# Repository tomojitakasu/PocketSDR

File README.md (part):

# **Pocket SDR - An Open-Source GNSS SDR,<br> ver. 0.22**

<div style="text-align: right;">
<strong>2026-11-03</strong>
</div>

---

## **Overview**

**Pocket SDR** is an open-source Global Navigation Satellite System (GNSS) receiver based
on software-defined radio (SDR) technology. It consists of RF frontend devices named
**Pocket SDR FE**, utilities for these devices, and GNSS SDR applications (APs) written
in Python, C, and C++. It supports almost all signals for **GPS**, **GLONASS**, **Galileo**,
**QZSS**, **BeiDou**, **NavIC**, and **SBAS**.

The Pocket SDR FE device includes 2, 4, or 8 RF frontend channels, supporting the
GNSS L1 band (1525 - 1610 MHz) or L2/L5/L6 bands (1160 - 1290 MHz). For these signal bands, refer to [**GNSS Signal Bands**](https://github.com/tomojitakasu/PocketSDR/blob/master/doc/signal_bands.pdf). Each RF channel
of the Pocket SDR FE device provides IF (intermediate-frequency) bandwidth of up to 36 MHz. The ADC sampling rate can be configured up to 32 Msps (FE 2CH) or 48 Msps (FE 4CH and FE 8CH).

Pocket SDR also includes utility programs to configure the Pocket SDR FE devices,
capture, and dump digitized IF data.
Additionally, Pocket SDR provides GNSS SDR APs to display the PSD (power spectrum density) of captured IF data, search for GNSS signals, track these signals, decode navigation data, and generate PVT (position, velocity, and time) solutions.
These utilities and APs are compatible with **Windows**, **Linux**, **Raspberry Pi OS**, **macOS**, and other environments.

The supported GNSS signals by Pocket SDR are as follows. For details on these signals and Pocket SDR signal IDs, refer to
[**GNSS Signals**](https://github.com/tomojitakasu/PocketSDR/blob/master/doc/signal_IDs.pdf).

* **GPS**: L1C/A, L1C-D, L1C-P, L2C-M, L5-I, L5-Q
* **GLONASS**: L1C/A (L1OF), L2C/A (L2OF), L1OCd, L1OCp, L2OCp, L3OCd, L3OCp
* **Galileo**: E1-B, E1-C, E5a-I, E5a-Q, E5b-I, E5b-Q, E5AltBOC (E5abQ), E6-B, E6-C
* **QZSS**: L1C/A, L1C/B, L1C-D, L1C-P, L1S, L2C-M, L5-I, L5-Q, L5S-I, L5S-Q, L6D, L6E
* **BeiDou**: B1I, B1C-D, B1C-P, B2a-D, B2a-P, B2I, B2b-I, B3I
* **NavIC**: L1-SPS-D, L1-SPS-P, L5-SPS
* **SBAS**: L1C/A, L5-I, L5-Q

These utilities and APs are written in Python, C, and C++ in a compact and modular way,
making them easy to modify for adding custom algorithms.

In addition to the Pocket SDR FE devices, Pocket SDR supports third-party
SDR hardware (**USRP**, **LimeSDR**, **bladRF**, **PlutoSDR**, **RTL-SDR**, and so on) via 
[**SoapySDR**](https://github.com/pothosware/SoapySDR/wiki).
See [**SoapySDR Device Notes**](https://github.com/tomojitakasu/PocketSDR/blob/master/doc/notes_soapy_dev.md) for verified devices,
installation notes, and device-specific caveats.

<p align="center">
  
  <b>Pocket SDR FE 2CH (v.2.0 and v.2.3), FE 4CH</b>
</p>

<p align="center">
  
  <b>Pocket SDR FE 8CH (2-RF-inputs and 8-RF-inputs)</b>
</p>

<p align="center">
  
  <b>GUI-based Real-Time GNSS SDR Receiver AP</b>
</p>

--------------------------------------------------------------------------------
<div class="pagebreak"></div>

## **Documents**

- Pocket SDR C Library API Reference
(https://github.com/tomojitakasu/PocketSDR/tree/master/doc/api_ref.pdf)

- Pocket SDR Command Reference
(https://github.com/tomojitakasu/PocketSDR/tree/master/doc/command_ref.pdf)

- Pocket SDR GNSS SDR Algorithm Description
(https://github.com/tomojitakasu/PocketSDR/tree/master/doc/algo_desc.pdf)

- Pocket SDR GNSS SDR アルゴリズム解説
(https://github.com/tomojitakasu/PocketSDR/tree/master/doc/algo_desc_jp.pdf)

- T.Takasu, An Open Source GNSS SDR: Development and Application, IPNTJ Next GNSS
Technology WG, February 21, 2022
(https://gpspp.sakura.ne.jp/paper2005/IPNTJ_NEXTWG_202202.pdf)

- T.Takasu, Development of QZSS L6 Receiver without Pilot Signal by using SDR,
IPNTJ Annual Conference, June 10, 2022
(https://gpspp.sakura.ne.jp/paper2005/IPNTJ_20220610.pdf)

- T.Takasu, Pocket SDR: Design, Implementation and Applications, A seminar for
GNSS Software Defined Receivers, Nov 19, 2024
(https://gpspp.sakura.ne.jp/paper2005/pocketsdr_seminar_202411_revA.pdf)

--------------------------------------------------------------------------------
<div class="pagebreak"></div>

## **Directory Structure and Contents**
```
PocketSDR
├── bin         # Pocket SDR APs binary programs
├── app         # Pocket SDR APs source programs
│   ├── pocket_conf  # Pocket SDR FE device configurator
│   ├── pocket_dump  # Dump digital IF data of Pocket SDR FE device
│   ├── pocket_scan  # Scan and list USB devices
│   ├── pocket_acq   # GNSS signal acquisition
│   ├── pocket_trk   # GNSS signal tracking and PVT generation
│   ├── pocket_web   # GNSS receiver server with Web UI
│   ├── pocket_snap  # Snapshot Positioning
│   ├── pocket_calib # Antenna array attitude / per-CH bias calibration
│   ├── convbin      # RINEX converter supporting Pocket SDR
│   └── str2str      # Stream converter (RTKLIB-derived)
├── src         # Pocket SDR library source programs
├── html        # Web UI files served by pocket_web (JS + CSS, no build step)
├── python      # Pocket SDR Python scripts (incl. pocket_sdr.py GUI)
├── lib         # Libraries for APs and Python scripts
│   ├── win32        # Built libraries for Windows (UCRT64)
│   ├── macos        # Built libraries for macOS
│   ├── linux        # Built libraries for Linux or Raspberry Pi OS
│   ├── build        # Makefiles to build libraries (UCRT64 / Linux / macOS)
│   ├── cyusb        # Cypress EZ-USB API (CyAPI.a) and includes
│   ├── RTKLIB       # RTKLIB source programs based on 2.4.3 b34
│   ├── pocketfft    # PocketFFT (header-only FFT, used internally)
│   └── SoapySDR     # SoapySDR headers + import lib for SDR device support
├── conf        # Configuration files for Pocket SDR FE
├── FE_2CH      # Pocket SDR FE 2CH H/W and F/W
├── FE_4CH      # Pocket SDR FE 4CH H/W and F/W
├── FE_8CH      # Pocket SDR FE 8CH H/W and F/W (3-bit RF samples)
├── driver      # Driver installation instruction for Pocket SDR FE
├── doc         # Documents (incl. api_ref.md, command_ref.md)
├── image       # Image files for documents
├── sample      # Sample digital IF data captured by Pocket SDR FE
└── test        # Test codes, scripts and data
    ├── python       # Python scripts for tests
    ├── script       # Shell scripts for tests
    ├── src          # source programs for tests
    └── utest        # makefile for unit tests

```
--------------------------------------------------------------------------------
<div class="pagebreak"></div>

## **Installation for Windows**

* Download and extract PocketSDR.zip or clone the git repository [**here**](https://github.com/tomojitakasu/PocketSDR) to an appropriate directory <install_dir>.
to an appropriate directory <install_dir>.
```
> unzip PocketSDR.zip
or
> git clone https://github.com/tomojitakasu/PocketSDR
```
* Install USB device driver for Pocket SDR FE according to [**driver/readme.txt**](https://github.com/tomojitakasu/PocketSDR/blob/master/driver/readme.txt)
.
* Install [**Python**](https://www.python.org/) with checking "Add python.exe to PATH".
* Install additional python packages as follows.
```
> pip install numpy scipy matplotlib
```
* (Optional) To use SoapySDR-supported devices (LimeSDR, HackRF, RTL-SDR,
  bladeRF, etc.), install [**radioconda**](https://github.com/ryanvolz/radioconda)
  and add `<radioconda_install_dir>\Library\bin` to PATH. See
  [SoapySDR Device Notes](https://github.com/tomojitakasu/PocketSDR/blob/master/doc/notes_soapy_dev.md#windows) for per-device
  packages, Zadig driver setup, and bladeRF version caveats.
* Add the Pocket SDR binary programs path (<install_dir>\PocketSDR\bin) to 
  the command search path (Path) of Windows environment variables.
* Add the Pocket SDR Python scripts path (<install_dir>\PocketSDR\python) to 
  the command search path (Path) of Windows environment variables.

--------------------------------------------------------------------------------

## **To rebuild binary programs for Windows**
* If you want to rebuild the binary utilities, APs, or shared libraries for the python APs
for Windows, you need [**MSYS2**](https://www.msys2.org/) with the **UCRT64** environment.
The UCRT64 toolchain links against the same C runtime (`ucrtbase.dll`) as
[**radioconda**](https://github.com/ryanvolz/radioconda)'s SoapySDR DLLs, which
gives stable high-rate streaming with SDR hardware (e.g., LimeSDR at 64 Msps).
The legacy **MINGW64** environment also builds, but suffers significant
performance loss with SoapySDR devices due to msvcrt/UCRT mixing.

* Open the **MSYS2 UCRT64** shell and install the development tools and the
  Python stack used by the python APs:
```
$ pacman -Syy
$ pacman -S git make
$ pacman -S mingw-w64-ucrt-x86_64-gcc
$ pacman -S mingw-w64-ucrt-x86_64-binutils
$ pacman -S mingw-w64-ucrt-x86_64-python
$ pacman -S mingw-w64-ucrt-x86_64-python-numpy
$ pacman -S mingw-w64-ucrt-x86_64-python-scipy
$ pacman -S mingw-w64-ucrt-x86_64-python-matplotlib
```
* If you intend to use SoapySDR-supported devices, install radioconda first.
  The default radioconda location used by the Makefiles is
  `/c/Users/<user>/radioconda/Library`. If installed elsewhere, override
  with `SOAPY_ROOT` on the make command line. See
  [SoapySDR Device Notes](https://github.com/tomojitakasu/PocketSDR/blob/master/doc/notes_soapy_dev.md#windows-build-notes)
  for details.

* If SoapySDR device support is not required, build `libsdr`, `pocket_trk`,
  and `pocket_dump` with `USE_SOAPY=0`. Pocket SDR FE USB devices and
  IF-file based processing still work; only SoapySDR device input is
  disabled. If you are rebuilding an existing tree, run `make clean` first.
```
$ cd <install_dir>/lib/build
$ make clean && make USE_SOAPY=0 && make install
$ cd <install_dir>/app/pocket_trk
$ make clean && make USE_SOAPY=0 && make install
$ cd <install_dir>/app/pocket_dump
$ make clean && make USE_SOAPY=0 && make install
```

* Move to the library build directory and build libraries.
```
$ cd <install_dir>/lib/build
$ make
$ make install
```
  The default radioconda location is `/c/Users/<user>/radioconda/Library`. If
  installed elsewhere, override on the command line:
```
$ make SOAPY_ROOT=/c/path/to/radioconda/Library
```

* Move to the application program directory and build utilities and APs.
```
$ cd <install_dir>/app
$ make
$ make install
```

* To run unit tests for the libraries:
```
$ cd <install_dir>/test/utest
$ make
$ make test
==> test_sdr_array.exe
test_sdr_array_new_free_api ... OK
test_sdr_array_ant_pos_api ... OK
t...
test_sdr_usb_req_control ... OK
```

--------------------------------------------------------------------------------
<div class="pagebreak"></div>

## **Installation for Linux or Raspberry Pi OS**

> **Note**: Pocket SDR has been verified on Ubuntu / Debian-based Linux
> distributions and on **Raspberry Pi OS (Bookworm) on Raspberry Pi 5**
> (aarch64). The Pi 5 has been confirmed to handle Pocket SDR FE and the
> apt-installed SoapySDR devices for typical L1 / L2 single-channel use;
> see the **Notes for Raspberry Pi 5** subsection below for hardware
> caveats (USB power, USB 3.0 routing, CPU limits).

* You need fundamental development packages and some libraries. Confirm the following
packages installed: git, gcc, g++, make, libusb-1.0-0-dev, libfftw3-dev, python3, python3-numpy,
python3-scipy, python3-matplotlib, python3-tk
* (Optional) To use SoapySDR-supported devices (LimeSDR, HackRF, RTL-SDR,
  SDRPlay, bladeRF, etc.), install SoapySDR and the per-device modules:
```
$ sudo apt install libsoapysdr-dev soapysdr-tools soapysdr-module-all
```
  See [SoapySDR Device Notes](https://github.com/tomojitakasu/PocketSDR/blob/master/doc/notes_soapy_dev.md#linux--raspberry-pi-os)
  for per-device package names, udev access, UHD image installation, and
  the Ubuntu 24.04 bladeRF module update workaround.

* Download and extract PocketSDR.zip or clone the git repository to an appropriate directory <install_dir>.
```
$ unzip PocketSDR.zip
or
$ git clone https://github.com/tomojitakasu/PocketSDR
```
* Move to the library build directory and build libraries.
```
$ cd <install_dir>/lib/build
$ make
$ make install
```
* Move to the application program directory and build utilities and APs.
```
$ cd <install_dir>/app
$ make
$ make install
```
* Add the Pocket SDR binary programs path (<install_dir>/PocketSDR/bin) to the command search path.

* (Recommended) Install the udev rule so the Pocket SDR FE device is
  accessible to a normal user account (no `sudo` required). The repository
  ships a ready-to-use rule at [`driver/99-pocket-sdr.rules`](https://github.com/tomojitakasu/PocketSDR/blob/master/driver/99-pocket-sdr.rules) that grants the
  `plugdev` group read/write access to Pocket SDR FE 2CH (Cypress
  EZ-USB FX2LP, VID `04B4` / PID `1004`) and FE 4CH / 8CH (Cypress
  EZ-USB FX3, VID `04B4` / PID `00F1`):
```
$ sudo cp <install_dir>/driver/99-pocket-sdr.rules /etc/udev/rules.d/
$ sudo udevadm control --reload-rules && sudo udevadm trigger
$ sudo usermod -aG plugdev $USER     # add yourself to plugdev
```
  Log out and back in (or reboot) so the new group membership takes effect,
  then unplug and re-plug the device. After that, `pocket_scan`,
  `pocket_conf`, `pocket_dump`, `pocket_trk`, and `pocket_sdr.py` all run
  without `sudo`.

  Verify the rule is in effect:
```
$ lsusb -d 04b4:                         # confirm the device is enumerated
$ ls -l /dev/bus/usb/<bus>/<dev>          # group should be "plugdev", mode 0660
$ pocket_scan                             # should list the device
```
  If your distribution uses a different group than `plugdev` (e.g.
  `dialout` on some systems, or systemd-logind's `uaccess` is sufficient
  on its own), adjust `GROUP=` in the rule file or rely on the
  `TAG+="uaccess"` line which grants access to the currently logged-in
  seat user on systemd-based systems.

* If you skip the udev rule, you must run the Pocket SDR utilities under
  `sudo` to access the USB device:
```
$ sudo pocket_conf ../conf/pocket_L1L6_12MHz.conf
$ sudo pocket_dump -t 10 ch1.bin ch2.bin
$ sudo pocket_sdr.py
```

### **Notes for Raspberry Pi 5**

Raspberry Pi 5 (Cortex-A76 4-core @ 2.4 GHz, aarch64) runs the same
build path as desktop Linux above. The Makefiles auto-detect aarch64
and enable NEON SIMD optimizations (`-DNEON`). A few Pi-specific
constraints to be aware of:

* **USB power budget**: Pi 5 advertises 5V / 5A on the official PSU but
  the USB ports share a ~1.6 A budget. USRP B210 (~2 A peak), Pocket
  SDR FE 8CH, and BladeRF 2.0 typically need either a USB Y-cable
  (separate +5V feed) or a **self-powered (externally-fed) USB hub**.
  Symptoms of insufficient power are intermittent USB resets, FPGA
  bitstream upload failures (USRP), and dropped samples.

* **USB 3.0 routing**: Pi 5 has 2× USB 3.0 + 2× USB 2.0 ports. Always
  connect high-rate SDRs (LimeSDR, USRP B210, Pocket SDR FE 8CH) to a
  USB 3.0 port. Verify enumeration speed with:
```
$ lsusb -t
```
  The relevant device should show `5000M` (USB 3.0) ? `480M` means the
  device fell back to USB 2.0, which is bandwidth-limited and will drop
  samples at high rates.

* **CPU / sample rate limits**: Pi 5 holds up well thanks to NEON SIMD
  acceleration. Measured load (`pocket_trk` realtime, single-band L1
  tracking, all-in-view PRNs):

  | Device | Sample rate × tracked channels | CPU load (of 400% = 4 cores) |
  |---|---|---|
  | LimeSDR USB | 32 Msps × 7 ch | ~280% |
  | USRP B210 | 32 Msps × 8 ch | ~290% |
  | PlutoSDR | 6 Msps × 10 ch | ~121% |
  | RTL-SDR | 2.4 Msps × 16 ch | ~102% |

  32 Msps with many tracked channels is workable but leaves limited
  headroom for additional bands or PVT processing. **8 Msps** is a
  comfortable sweet spot for general L1 use on Pi 5. Heavier configs
  (LimeSDR 60 Msps × 2-band, Pocket SDR FE 8CH × multi-band) will
  saturate the Pi 5 CPU and are intended for desktop use.

* **PocketFFT vs FFTW3**: PocketFFT (default) works on aarch64 with
  NEON. If FFT becomes a bottleneck for your workload, FFTW3 is
  marginally faster on large transforms ? install with
  `sudo apt install libfftw3-dev` and switch the build per the
  [Using FFTW3 instead of PocketFFT](#using-fftw3-instead-of-pocketfft-optional)
  section below.

* **Storage**: For long IF data captures (`pocket_dump -t <long>`,
  `pocket_trk -raw`), use a USB 3.0 SSD or NVMe HAT. The microSD card
  on stock Pi 5 cannot sustain >50 MB/s writes for extended periods
  and will drop samples.

--------------------------------------------------------------------------------
<div class="pagebreak"></div>

## **Installation for macOS**

> **Note**: Verified on Apple Silicon (arm64). Pocket SDR FE 2/4/8CH (USB)
> has been confirmed working. For SoapySDR devices on macOS, see
> [SoapySDR Device Notes](https://github.com/tomojitakasu/PocketSDR/blob/master/doc/notes_soapy_dev.md#macos).

* You need [**Homebrew**](https://brew.sh) as a base package manager. Install
  Homebrew by following the instructions on its site, then install
  development tools:
```
$ brew install libusb fftw
```

* (Optional) Install [**radioconda**](https://github.com/ryanvolz/radioconda)
  to use SoapySDR devices and a self-contained Python environment:
```
$ curl -L -O https://github.com/ryanvolz/radioconda/releases/latest/download/Radioconda-MacOSX-arm64.sh
$ bash Radioconda-MacOSX-arm64.sh
```
  For Intel mac use `Radioconda-MacOSX-x86_64.sh`. Known macOS SoapySDR
  packaging workarounds are collected in
  [SoapySDR Device Notes](https://github.com/tomojitakasu/PocketSDR/blob/master/doc/notes_soapy_dev.md#macos).

* Download and extract PocketSDR.zip or clone the git repository to an
  appropriate directory <install_dir>.
```
$ unzip PocketSDR.zip
or
$ git clone https://github.com/tomojitakasu/PocketSDR
```
* Build libraries and applications. The Makefiles auto-detect Apple
  Silicon (`Darwin arm64`) and use `clang++` for C++ sources and pull
  Homebrew's `libusb` / `fftw` headers from `/opt/homebrew/include`:
```
$ cd <install_dir>/lib/build
$ make
$ make install
$ cd <install_dir>/app
$ make
$ make install
```
* Add `<install_dir>/PocketSDR/bin` to the command search path.

* For SoapySDR-supported devices, use the driver shortcuts in
  `<install_dir>/app/pocket_trk/pocket_trk.sh`. See
  [SoapySDR Device Notes](https://github.com/tomojitakasu/PocketSDR/blob/master/doc/notes_soapy_dev.md#runtime-driver-shortcuts).

* Pocket SDR FE 2CH / 4CH / 8CH USB devices work on macOS via libusb-1.0
  with **no driver install needed** (Apple's IOUSB stack provides
  raw USB access through libusb). Plug in the device and run:
```
$ pocket_scan                                          # device should be listed
$ pocket_conf <install_dir>/conf/pocket_L1L6_12MHz.conf
$ pocket_dump -t 10 ch1.bin ch2.bin
```

--------------------------------------------------------------------------------
<div class="pagebreak"></div>

## **Using FFTW3 instead of PocketFFT (optional)**

Starting from version 0.15b, Pocket SDR ships with [**PocketFFT**](https://gitlab.mpcdf.mpg.de/mtr/pocketfft) (BSD-3-Clause) as the default FFT backend, replacing [**FFTW3**](https://www.fftw.org/) (GPL). The change is licensing-driven; for most workloads PocketFFT is competitive, but FFTW3 is still slightly faster on large transforms and supports runtime wisdom (auto-tuned plans) ? `pocket_trk` / `pocket_snap` / `pocket_acq` can read `python/fftw_wisdom.txt` for further speed-up.

To build with FFTW3 instead, install the library and build `libsdr` and the
FFT-using applications with `USE_FFTW=1`.

* Install FFTW3 (single-precision):
```
$ pacman -S mingw-w64-ucrt-x86_64-fftw    # MSYS2 UCRT64 (Windows)
$ sudo apt install libfftw3-dev           # Ubuntu / Debian / Raspberry Pi OS
$ brew install fftw                       # macOS
```
* Rebuild from scratch:
```
$ cd <install_dir>/lib/build
$ make clean && make USE_FFTW=1 && make USE_FFTW=1 install
$ cd <install_dir>/app/pocket_acq
$ make clean && make USE_FFTW=1 && make install
$ cd <install_dir>/app/pocket_snap
$ make clean && make USE_FFTW=1 && make install
$ cd <install_dir>/app/pocket_calib
$ make clean && make USE_FFTW=1 && make install
$ cd <install_dir>/app/pocket_dump
$ make clean && make USE_FFTW=1 && make install
$ cd <install_dir>/app/pocket_trk
$ make clean && make USE_FFTW=1 && make install
```
* (Optional, FFTW3 only) Generate a wisdom file tuned for the host CPU. Once present, `pocket_trk`, `pocket_snap`, and `pocket_acq` pick it up automatically.
```
$ cd <install_dir>/app/pocket_trk
$ ./fftw_wisdom -n 4096
$ cp fftw_wisdom.txt ../../python/
```

Note: FFTW3 is GPL-licensed, so a binary linked against it inherits GPL terms. Keep this in mind when redistributing.

--------------------------------------------------------------------------------
<div class="pagebreak"></div>

## **Using AVX-512 instructions (optional)**

On x86-64 CPUs with AVX-512 (AMD Zen 4 or later such as Ryzen 9000 series,
Intel Ice Lake or later), `libsdr` can be built with `USE_AVX512=1` to use the
AVX-512 versions of the carrier mixer, correlator, LPF and array covariance
kernels (`-DAVX512`) instead of the default AVX2 ones. The APs link `libsdr`
statically, so rebuild them after the library. A binary built with
`USE_AVX512=1` does not run on a CPU without AVX-512.
```
$ cd <install_dir>/lib/build
$ make clean && make USE_AVX512=1 && make install
$ cd <install_dir>/app
$ make clean && make && make install
```
The unit tests can be built with the same option: `make -C test/utest USE_AVX512=1`.

--------------------------------------------------------------------------------
<div class="pagebreak"></div>

## **GNSS SDR Utilities and APs**

Pocket SDR includes the following utilities for the Pocket SDR FE.

- **pocket_scan**: Scans and lists USB Devices.
- **pocket_conf**: Configures Pocket SDR FE device.
- **pocket_dump**: Captures and dumps IF data from the Pocket SDR FE device

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
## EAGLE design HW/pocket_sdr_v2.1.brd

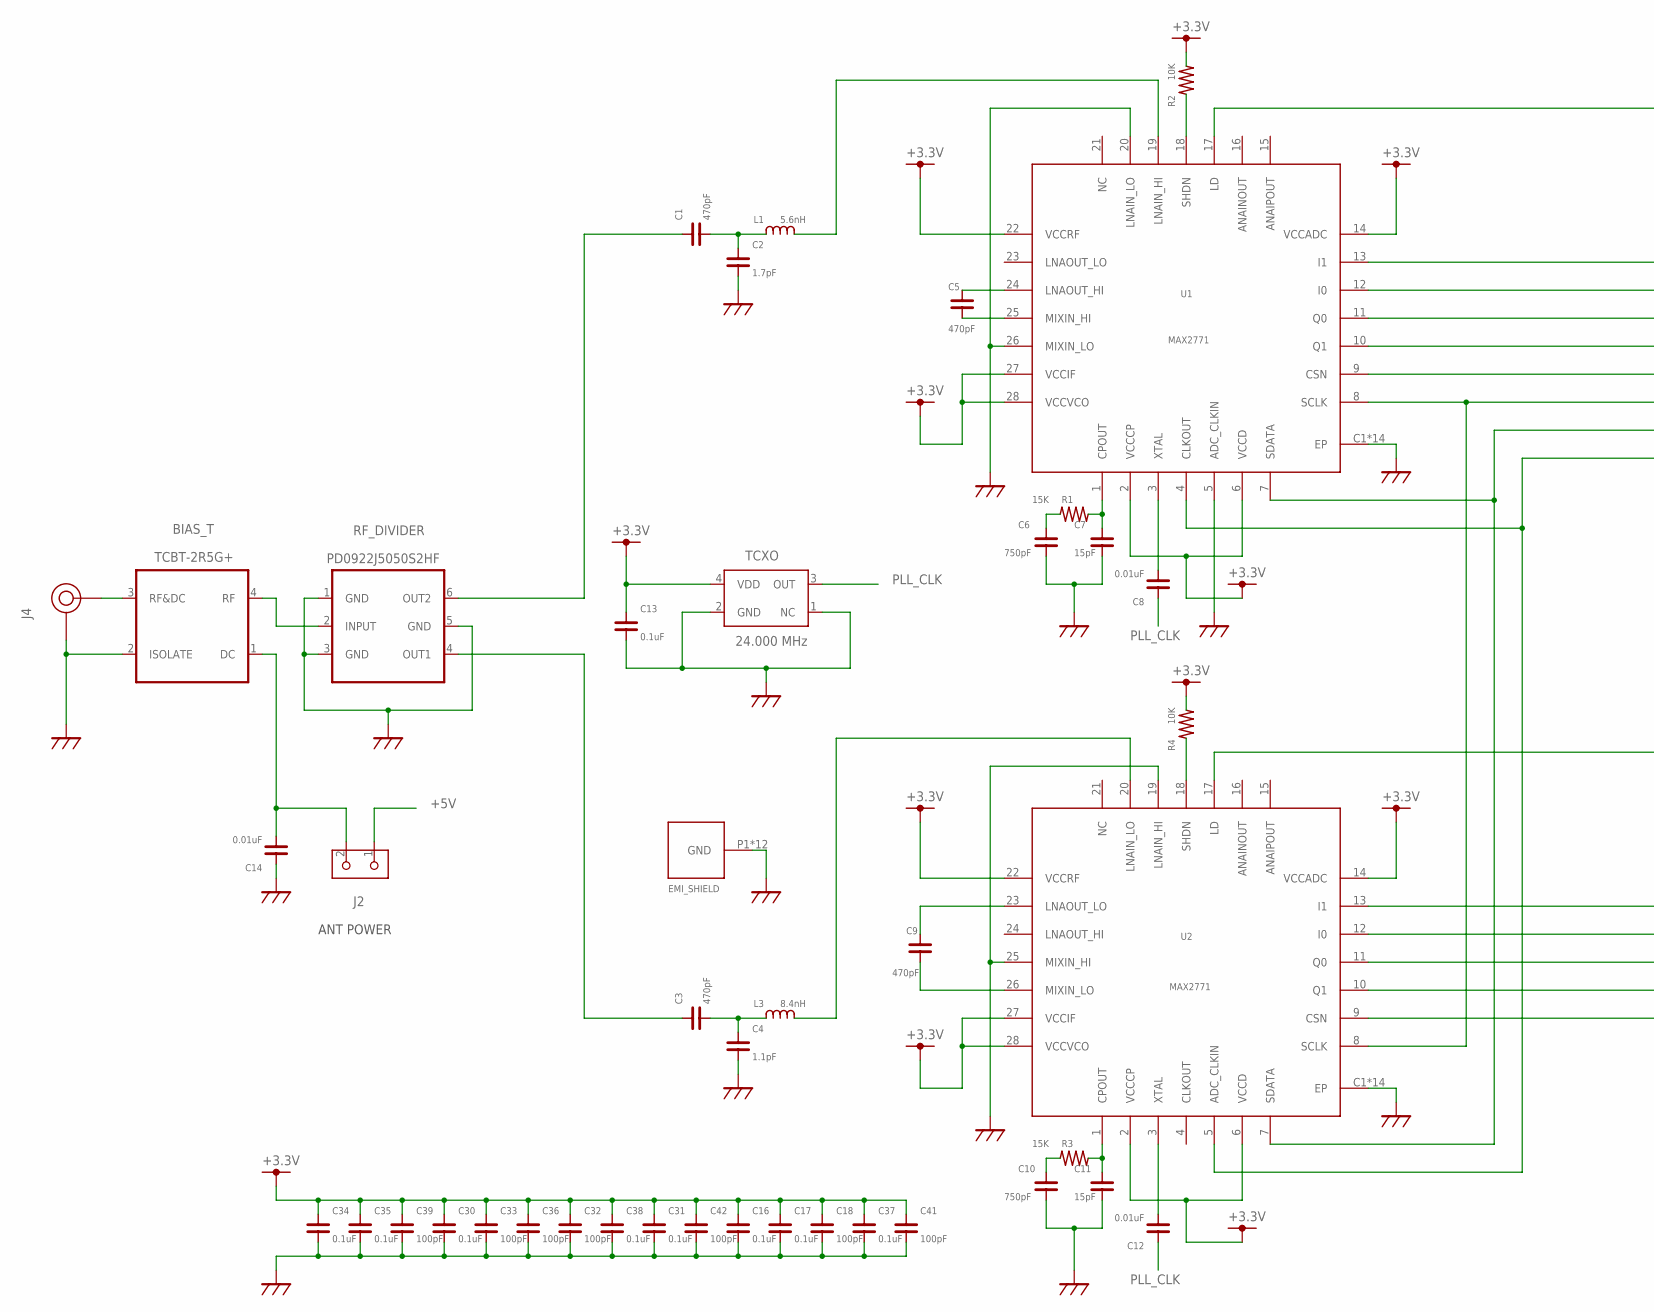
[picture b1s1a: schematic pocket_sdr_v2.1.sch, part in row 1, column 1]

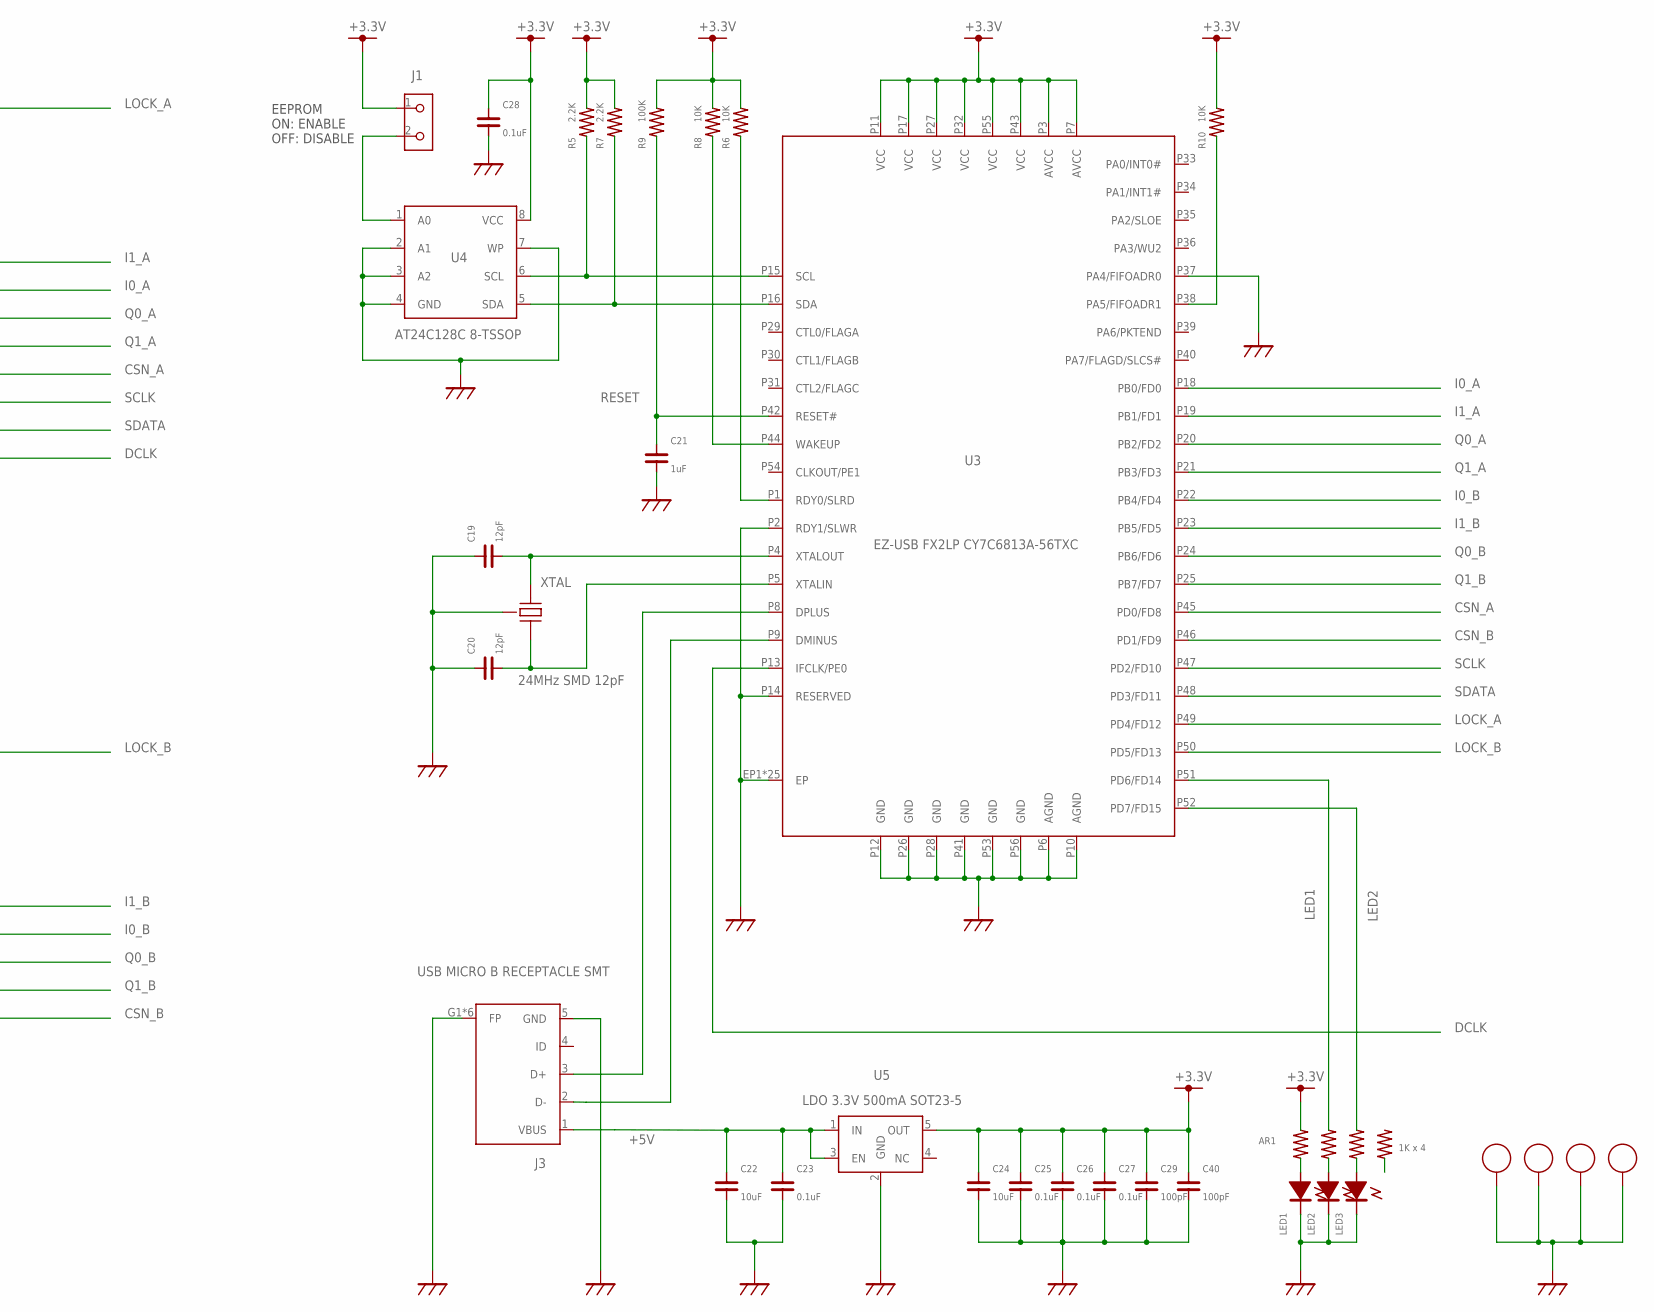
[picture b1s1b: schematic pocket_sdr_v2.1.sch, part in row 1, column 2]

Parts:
AR1: 1K x 4; EXB28V
BIAS_T: TCBT-2R5G+; BIAS_T
C1, C3, C5, C9: 470pF; C1005
C2: 1.7pF; C1005
C4: 1.1pF; C1005
C6, C10: 750pF; C1005
C7, C11: 15pF; C1005
C8, C12, C14: 0.01uF; C1005
C13, C16, C17, C23, C25, C26, C27, C28, C30, C31, C34, C35, C37, C38: 0.1uF; C1005
C18, C29, C32, C33, C36, C39, C40, C41, C42: 100pF; C1005
C19, C20: 12pF; C1005
C21: 1uF; C1005
C22, C24: 10uF; C3225
J1, J2: PIN HEADER 2MM 2P; PINH-2MM-2P
J3: USB MICRO B RECEPTACLE SMT; MICROUSB
J4: SMA JACK EDGE MNT; SMA-ANG
L1: 5.6nH; C1608
L3: 8.4nH; C1608
LED1: LED1608 GREEN; LED_1608
LED2, LED3: LED1608 BLUE; LED_1608
R1, R3: 15K; C1005
R2, R4, R6, R8, R10: 10K; C1005
R5, R7: 2.2K; C1005
R9: 100K; C1005
RF-SHEILD-CASE: BMI-S-202-F BMI-S-202-C; BMI-S-202
RF_DIVIDER: PD0922J5050S2HF; RF_DIV
TCXO: 24.000 MHz; TCXO
U1, U2: MAX2771; TQFN28
U3: EZ-USB FX2LP CY7C6813A-56TXC; QFN56
U4: AT24C128C 8-TSSOP; TSSOP_8P
U5: LDO 3.3V 500mA SOT23-5; SOT23
U$53, U$54, U$55, U$58: CPAD_2.2MM
XTAL: 24MHz SMD 12pF; XTAL_SMD

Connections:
+3.3V: AR1.2, C13.1, C16.1, C17.1, C18.1, C24.P$1 (1), C25.1, C26.1, C27.1, C28.1, C29.1, C30.1, C31.1, C32.1, C33.1, C34.1, C35.1, C36.1, C37.1, C38.1, C39.1, C40.1, C41.1, C42.1, J1.1, R2.2, R4.2, R5.2, R6.2, R7.2, R8.2, R9.2, R10.2, TCXO.4 (VDD), U1.2 (VCCCP), U1.6 (VCCD), U1.14 (VCCADC), U1.22 (VCCRF), U1.27 (VCCIF), U1.28 (VCCVCO), U2.2 (VCCCP), U2.6 (VCCD), U2.14 (VCCADC), U2.22 (VCCRF), U2.27 (VCCIF), U2.28 (VCCVCO), U3.P3 (AVCC), U3.P7 (AVCC), U3.P11 (VCC), U3.P17 (VCC), U3.P27 (VCC), U3.P32 (VCC), U3.P43 (VCC), U3.P55 (VCC), U4.8 (VCC), U5.5 (OUT)
+5V: C22.P$1 (1), C23.1, J2.1, J3.1 (VBUS), U5.1 (IN), U5.3 (EN)
CSN_A: U1.9 (CSN), U3.P45 (PD0/FD8)
CSN_B: U2.9 (CSN), U3.P46 (PD1/FD9)
DCLK: U1.4 (CLKOUT), U2.5 (ADC_CLKIN), U3.P13 (IFCLK/PE0)
FIFOADR1: R10.1, U3.P38 (PA5/FIFOADR1)
GND: BIAS_T.2 (ISOLATE), C2.1, C4.2, C6.2, C7.2, C10.2, C11.2, C13.2, C14.1, C16.2, C17.2, C18.2, C19.1, C20.1, C21.2, C22.P$2 (2), C23.2, C24.P$2 (2), C25.2, C26.2, C27.2, C28.2, C29.2, C30.2, C31.2, C32.2, C33.2, C34.2, C35.2, C36.2, C37.2, C38.2, C39.2, C40.2, C41.2, C42.2, J3.5 (GND), J3.G1 (FP), J3.G2 (FP), J3.G3 (FP), J3.G4 (FP), J3.G5 (FP), J3.G6 (FP), J4.P2 (GND), J4.P3 (GND), J4.P4 (GND), J4.P5 (GND), LED1.2, LED2.2, LED3.2, RF-SHEILD-CASE.P1, RF-SHEILD-CASE.P2, RF-SHEILD-CASE.P3, RF-SHEILD-CASE.P4, RF-SHEILD-CASE.P5, RF-SHEILD-CASE.P6, RF-SHEILD-CASE.P7, RF-SHEILD-CASE.P8, RF-SHEILD-CASE.P9, RF-SHEILD-CASE.P10, RF-SHEILD-CASE.P11, RF-SHEILD-CASE.P12, RF_DIVIDER.1 (GND), RF_DIVIDER.3 (GND), RF_DIVIDER.5 (GND), TCXO.1 (NC), TCXO.2 (GND), U1.5 (ADC_CLKIN), U1.20 (LNAIN_LO), U1.26 (MIXIN_LO), U1.C1 (EP), U1.C2 (EP), U1.C3 (EP), U1.C4 (EP), U1.EP, U1.V1 (EP), U1.V2 (EP), U1.V3 (EP), U1.V4 (EP), U1.V5 (EP), U1.V6 (EP), U1.V7 (EP), U1.V8 (EP), U1.V9 (EP), U2.19 (LNAIN_HI), U2.25 (MIXIN_HI), U2.C1 (EP), U2.C2 (EP), U2.C3 (EP), U2.C4 (EP), U2.EP, U2.V1 (EP), U2.V2 (EP), U2.V3 (EP), U2.V4 (EP), U2.V5 (EP), U2.V6 (EP), U2.V7 (EP), U2.V8 (EP), U2.V9 (EP), U3.EP1 (EP), U3.EP2 (EP), U3.EP3 (EP), U3.EP4 (EP), U3.EP5 (EP), U3.P2 (RDY1/SLWR), U3.P6 (AGND), U3.P10 (AGND), U3.P12 (GND), U3.P14 (RESERVED), U3.P26 (GND), U3.P28 (GND), U3.P37 (PA4/FIFOADR0), U3.P41 (GND), U3.P53 (GND), U3.P56 (GND), U3.P$1 (EP), U3.P$2 (EP), U3.P$3 (EP), U3.P$4 (EP), U3.P$5 (EP), U3.P$6 (EP), U3.P$7 (EP), U3.P$8 (EP), U3.P$9 (EP), U3.P$10 (EP), U3.P$11 (EP), U3.P$12 (EP), U3.P$13 (EP), U3.P$14 (EP), U3.P$15 (EP), U3.P$16 (EP), U3.P$17 (EP), U3.P$18 (EP), U3.P$19 (EP), U3.P$20 (EP), U4.2 (A1), U4.3 (A2), U4.4 (GND), U4.7 (WP), U5.2 (GND), U$53.EP, U$54.EP, U$55.EP, U$58.EP, XTAL.P2 (GND), XTAL.P4 (GND)
I0_A: U1.12 (I0), U3.P18 (PB0/FD0)
I0_B: U2.12 (I0), U3.P22 (PB4/FD4)
I1_A: U1.13 (I1), U3.P19 (PB1/FD1)
I1_B: U2.13 (I1), U3.P23 (PB5/FD5)
LED1: AR1.4, U3.P51 (PD6/FD14)
LED2: AR1.6, U3.P52 (PD7/FD15)
LOCK_A: U1.17 (LD), U3.P49 (PD4/FD12)
LOCK_B: U2.17 (LD), U3.P50 (PD5/FD13)
unnamed: C5.2, U1.25 (MIXIN_HI)
unnamed: C5.1, U1.24 (LNAOUT_HI)
unnamed: BIAS_T.3 (RF&DC), J4.P1 (RF)
unnamed: BIAS_T.4 (RF), RF_DIVIDER.2 (INPUT)
unnamed: BIAS_T.1 (DC), C14.2, J2.2
unnamed: R6.1, U3.P1 (RDY0/SLRD)
unnamed: AR1.3, LED2.1 (+)
unnamed: C1.2, C2.2, L1.1
unnamed: C8.2, U1.3 (XTAL)
unnamed: L1.2, U1.19 (LNAIN_HI)
unnamed: AR1.1, LED1.1 (+)
unnamed: C1.1, RF_DIVIDER.6 (OUT2)
unnamed: C9.2, U2.26 (MIXIN_LO)
unnamed: C9.1, U2.23 (LNAOUT_LO)
unnamed: C19.2, U3.P4 (XTALOUT), XTAL.P1 (XTAL1)
unnamed: R2.1, U1.18 (SHDN)
unnamed: J3.3 (D+), U3.P8 (DPLUS)
unnamed: C20.2, U3.P5 (XTALIN), XTAL.P3 (XTAL2)
unnamed: AR1.5, LED3.1 (+)
unnamed: C7.1, R1.2, U1.1 (CPOUT)
unnamed: C6.1, R1.1
unnamed: C11.1, R3.2, U2.1 (CPOUT)
unnamed: R7.1, U3.P16 (SDA), U4.5 (SDA)
unnamed: R5.1, U3.P15 (SCL), U4.6 (SCL)
unnamed: R8.1, U3.P44 (WAKEUP)
unnamed: C10.1, R3.1
unnamed: J3.2 (D-), U3.P9 (DMINUS)
unnamed: J1.2, U4.1 (A0)
unnamed: C3.1, RF_DIVIDER.4 (OUT1)
unnamed: C3.2, C4.1, L3.1
unnamed: L3.2, U2.20 (LNAIN_LO)
unnamed: R4.1, U2.18 (SHDN)
unnamed: C12.2, U2.3 (XTAL)
PLL_CLK: C8.1, C12.1, TCXO.3 (OUT)
Q0_A: U1.11 (Q0), U3.P20 (PB2/FD2)
Q0_B: U2.11 (Q0), U3.P24 (PB6/FD6)
Q1_A: U1.10 (Q1), U3.P21 (PB3/FD3)
Q1_B: U2.10 (Q1), U3.P25 (PB7/FD7)
RESET: C21.1, R9.1, U3.P42 (RESET#)
SCLK: U1.8 (SCLK), U2.8 (SCLK), U3.P47 (PD2/FD10)
SDATA: U1.7 (SDATA), U2.7 (SDATA), U3.P48 (PD3/FD11)

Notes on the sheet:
ANT POWER
EEPROM ON: ENABLE OFF: DISABLE

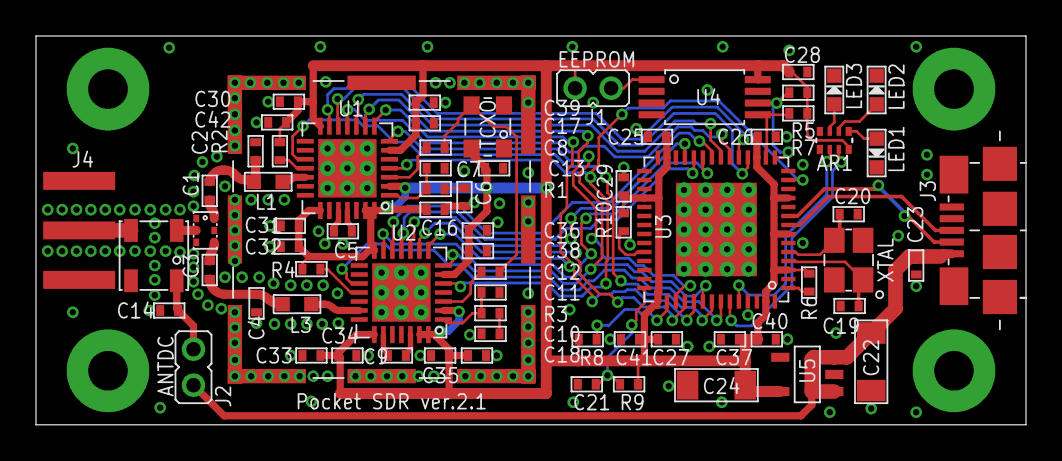
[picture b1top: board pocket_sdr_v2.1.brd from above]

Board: 2 copper layers, 55.0 x 21.6 mm, 75 parts (0 on the bottom side), 56 nets.

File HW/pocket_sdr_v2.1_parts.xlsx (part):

No | Part | Value | Package | Assembly | Supplier | Supplier Part # | Digi-Key Part # | Price(Yen) | URL | NOTE
1 | U1 | MAX2771 | TQFN28 | 1 | Maxim | MAX2771ETI+ | MAX2771ETI+-ND | 1012 | https://www.digikey.jp/products/ja?keywords=MAX2771ETI%2B-ND
2 | U2 | MAX2771 | TQFN28 | 1 | Maxim | MAX2771ETI+ | MAX2771ETI+-ND | 1012 | https://www.digikey.jp/products/ja?keywords=MAX2771ETI%2B-ND
3 | U3 | EZ-USB FX2LP QFN56 | QFN56 | 1 | Cypress | CY7C68013A-56LTXCT | 428-4634-1-ND | 1702 | https://www.digikey.jp/product-detail/ja/cypress-semiconduct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
4 | U4 | EEPROM 128Kbit I2C 8TSSOP | TSSOP_8P | 1 | Microchip | AT24C128C-XHM-T | AT24C128C-XHM-TCT-ND | 59 | https://www.digikey.jp/product-detail/ja/microchip-technolog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
5 | U5 | LDO 3.3V 500mA SOT23-5 | SOT23-5 | 1 | RICOH | RP111N331D-TR-FE | 2129-RP111N331D-TR-FECT-ND | 138 | https://www.digikey.jp/products/ja?keywords=2129-RP111N331D-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
6 | BIAS_T | BIas Tee 50ohm 20 - 2500 MHz | 0.15" x 0.15" SMD | 1 | Mini-Circuits | TCBT-2R5G+ | - | 778.4 | https://www.minicircuits.com/WebStore/dashboard.html?model=T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
7 | RF_DIVIDER | 0805 Power Divider 50ohm 950 - 2150 MHz | 2.04 x 1.29 SMD | 1 | Anaren | PD0922J5050S2HF | 1173-1094-1-ND | 118 | https://www.digikey.jp/product-detail/ja/anaren/PD0922J5050S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
8 | TCXO | TCXO 24.000 MHz | 3.2 x 2.5 SMD | 1 | Epson | TG2520SMN 24.0000M-MCGNNM3 | - | 236 | https://www.mouser.jp/ProductDetail/Epson-Timing/TG2520SMN-2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
9 | XTAL | XTAL 24MHz SMD 12pF | 3.4 x 2.7 SMD | 1 | Wurth | 830108340709 | 1923-830108340709CT-ND | 57 | https://www.digikey.jp/products/ja?keywords=1923-830108340709CT-ND
10 | R1 | 15K | R1005 | 1 | YAGEO | RC0402JR-0715KL | 311-15KJRCT-ND | 1.6
11 | R2 | 10K | R1005 | 1 | YAGEO | RC0402JR-0710KL | 311-10KJRCT-ND | 1.6
12 | R3 | 15K | R1005 | 1 | YAGEO | RC0402JR-0715KL | 311-15KJRCT-ND | 1.6
13 | R4 | 10K | R1005 | 1 | YAGEO | RC0402JR-0710KL | 311-10KJRCT-ND | 1.6
14 | R5 | 2.2K | R1005 | 1 | YAGEO | RC0402JR-072K2L | 311-2.2KJRCT-ND | 1.6
15 | R6 | 10K | R1005 | 1 | YAGEO | RC0402JR-0710KL | 311-10KJRCT-ND | 1.6
16 | R7 | 2.2K | R1005 | 1 | YAGEO | RC0402JR-072K2L | 311-2.2KJRCT-ND | 1.6
17 | R8 | 10K | R1005 | 1 | YAGEO | RC0402JR-0710KL | 311-10KJRCT-ND | 1.6
18 | R9 | 100K | R1005 | 1 | YAGEO | RC0402JR-07100KL | 311-100KJRCT-ND | 1.6
19 | R10 | 10K | R1005 | 1 | YAGEO | RC0402JR-0710KL | 311-10KJRCT-ND | 1.6
20 | AR1 | 1K x 4 RES ARRAY | EXB28V | 1 | Panasonic | EXB-28V102JX | Y7102CT-ND | 12 | https://www.digikey.jp/products/ja?keywords=Y7102CT-ND
21 | C1 | 470pF | C1005 | 1 | Kyocera | 04025C471KAT2A | 478-1097-1-ND | 4.2
22 | C2 | 1.7pF | C1005 | 1 | Murata | GJM1555C1H1R7BB01D | 490-6074-1-ND | 16.600000000000001
23 | C3 | 470pF | C1005 | 1 | Kyocera | 04025C471KAT2A | 478-1097-1-ND | 4.2
24 | C4 | 1.1pF | C1005 | 1 | YAGEO | CC0402BRNPO9BN1R1 | 311-3321-1-ND | 5.7
25 | C5 | 470pF | C1005 | 1 | Kyocera | 04025C471KAT2A | 478-1097-1-ND | 4.2
26 | C6 | 750pF | C1005 | 1 | Taiyo Yuden | UMK105CH751JVHF | 587-5098-1-ND | 9.6999999999999993
27 | C7 | 15pF | C1005 | 1 | Kyocera | 04025A150JAT2A | 478-1072-1-ND | 5.4
28 | C8 | 0.01uF | C1005 | 1 | Kyocera | 0402YC103KAT2A | 478-1114-1-ND | 1.8
29 | C9 | 470pF | C1005 | 1 | Kyocera | 04025C471KAT2A | 478-1097-1-ND | 4.2
30 | C10 | 750pF | C1005 | 1 | Taiyo Yuden | UMK105CH751JVHF | 587-5098-1-ND | 9.6999999999999993
31 | C11 | 15pF | C1005 | 1 | Kyocera | 04025A150JAT2A | 478-1072-1-ND | 5.4
32 | C12 | 0.01uF | C1005 | 1 | Kyocera | 0402YC103KAT2A | 478-1114-1-ND | 1.8
33 | C13 | 0.1uF | C1005 | 1 | Kyocera | 0402YC104KAT2A | 478-7888-1-ND | 2
34 | C14 | 0.01uF | C1005 | 1 | Kyocera | 0402YC103KAT2A | 478-1114-1-ND | 1.8
35 | C16 | 0.1uF | C1005 | 1 | Kyocera | 0402YC104KAT2A | 478-7888-1-ND | 2
36 | C17 | 0.1uF | C1005 | 1 | Kyocera | 0402YC104KAT2A | 478-7888-1-ND | 2
37 | C18 | 100pF | C1005 | 1 | Kyocera | 04025A101JAT2A | 478-1082-1-ND | 3.4
38 | C19 | 12pF | C1005 | 1 | Kyocera | 04025A120JAT2A | 478-1071-1-ND | 1.6
39 | C20 | 12pF | C1005 | 1 | Kyocera | 04025A120JAT2A | 478-1071-1-ND | 1.6
40 | C21 | 1uF | C1005 | 1 | Kyocera | 0402ZD105KAT2A | 478-4596-1-ND | 10.5
41 | C22 | 10uF | C3216 | 1 | Samsung | CL31B106MOHNNNE | 1276-6641-1-ND | 18.8
42 | C23 | 0.1uF | C1005 | 1 | Kyocera | 0402YC104KAT2A | 478-7888-1-ND | 2
43 | C24 | 10uF | C3216 | 1 | Samsung | CL31B106MOHNNNE | 1276-6641-1-ND | 18.8
44 | C25 | 0.1uF | C1005 | 1 | Kyocera | 0402YC104KAT2A | 478-7888-1-ND | 2
45 | C26 | 0.1uF | C1005 | 1 | Kyocera | 0402YC104KAT2A | 478-7888-1-ND | 2
46 | C27 | 0.1uF | C1005 | 1 | Kyocera | 0402YC104KAT2A | 478-7888-1-ND | 2
47 | C28 | 0.1uF | C1005 | 1 | Kyocera | 0402YC104KAT2A | 478-7888-1-ND | 2
48 | C29 | 100pF | C1005 | 1 | Kyocera | 04025A101JAT2A | 478-1082-1-ND | 3.4
49 | C30 | 0.1uF | C1005 | 1 | Kyocera | 0402YC104KAT2A | 478-7888-1-ND | 2
50 | C31 | 0.1uF | C1005 | 1 | Kyocera | 0402YC104KAT2A | 478-7888-1-ND | 2
51 | C32 | 100pF | C1005 | 1 | Kyocera | 04025A101JAT2A | 478-1082-1-ND | 3.4
52 | C33 | 100pF | C1005 | 1 | Kyocera | 04025A101JAT2A | 478-1082-1-ND | 3.4
53 | C34 | 0.1uF | C1005 | 1 | Kyocera | 0402YC104KAT2A | 478-7888-1-ND | 2
54 | C35 | 0.1uF | C1005 | 1 | Kyocera | 0402YC104KAT2A | 478-7888-1-ND | 2
55 | C36 | 100pF | C1005 | 1 | Kyocera | 04025A101JAT2A | 478-1082-1-ND | 3.4
56 | C37 | 0.1uF | C1005 | 1 | Kyocera | 0402YC104KAT2A | 478-7888-1-ND | 2
57 | C38 | 0.1uF | C1005 | 1 | Kyocera | 0402YC104KAT2A | 478-7888-1-ND | 2
58 | C39 | 100pF | C1005 | 1 | Kyocera | 04025A101JAT2A | 478-1082-1-ND | 3.4
59 | C40 | 100pF | C1005 | 1 | Kyocera | 04025A101JAT2A | 478-1082-1-ND | 3.4
60 | C41 | 100pF | C1005 | 1 | Kyocera | 04025A101JAT2A | 478-1082-1-ND | 3.4
61 | C42 | 100pF | C1005 | 1 | Kyocera | 04025A101JAT2A | 478-1082-1-ND | 3.4
62 | L1 | 5.6nH | L1608 | 1 | Murata | LQW18AN5N6D00D | 490-1164-1-ND | 19
63 | L3 | 8.4nH | L1608 | 1 | Murata | LQW18AN8N4C8ZD | 490-15752-1-ND | 36
64 | LED1 | LED1608 GREEN | LED1608 | 1 | Kingbright | APT1608SGC | 754-1121-1-ND | 44
65 | LED2 | LED1608 White | LED1608 | 1 | QT Brightek | QBLP601-IW | 1516-1057-1-ND | 49
66 | LED3 | LED1608 White | LED1608 | 1 | QT Brightek | QBLP601-IW | 1516-1057-1-ND | 49
67 | J1 | PIN HEADER 2MM 2P | PINH-2MM-2P | 0 | Harwin | M22-2510205 | 952-1311-ND | 20
68 | J2 | PIN HEADER 2MM 2P | PINH-2MM-2P | 0 | Harwin | M22-2510205 | 952-1311-ND | 20
69 | J3 | USB MICRO B RECEPTACLE SMT | MICRO B SMT | 1 | Amphenol ICC | 10118192-0001LF | 609-4613-1-ND | 54 | https://www.digikey.jp/products/ja?keywords=609-4613-1-ND
70 | J4 | SMA JACK EDGE MNT | SMA JACK EDGE MNT | 0 | RF Solution | CON-SMA-EDGE-S | CON-SMA-EDGE-S-ND | 202 | https://www.digikey.jp/products/ja?keywords=CON-SMA-EDGE-S-ND
71 | J1-S | CONN SHUNT 2MM | CONN SHUNT 2MM | 0 | Sullins Connector | SPN02SYBN-RC | S3404-ND | 16
72 | J2-S | CONN SHUNT 2MM | CONN SHUNT 2MM | 0 | Sullins Connector | SPN02SYBN-RC | S3404-ND | 16
73 | RF-SHEILD-CASE | RF SHIELD 0.65" x 0.65" SOLDER | 0.65" x 0.65" | 0 | Laird | BMI-S-202-F | 903-1051-1-ND | 192 | https://www.digikey.jp/products/ja?keywords=903-1051-1-ND
74 | RF-SHEILD-CASE-C | RF SHIELD 0.668"x0.668" SNAP FIT | 0.668" x 0.668" | 0 | Laird | BMI-S-202-C | 903-1014-ND | 193 | https://www.digikey.jp/products/ja?keywords=903-1014-ND
75
 | Subtotal |  |  | 67 |  |  |  | 6235
77 | PCB | FR4 1.6mm 2 layer 21.6 x 55 mm |  |  | Fusion PCB |  |  | 242.48000000000002 | https://www.fusionpcb.jp/ | 10 pcs
78 | PCB Assembly |  |  |  | Fusion PCB |  |  | 2998.7999999999997 | https://www.fusionpcb.jp/ | 10 pcs
 | Case
79 | Aluminum Pipe | 25 x 15 x 1.5 x 55 mm |  |  | Yokoyama Techno |  |  | 150 | https://www.yokoyama-techno.net/detail/50.html | 10 pcs
80 | Panel | 25 x 15 mm Nylon white, Front, Back |  |  | DMM.make 3D print |  |  | 338.83333333333331 | https://make.dmm.com/print/ | 6 pcs
81 | Screw | M2 x 10 x 4 Sara |  |  | Monotaro |  |  | 25.117714285714285 | https://www.monotaro.com/p/0832/7435
82 | Nut | M2 x 4 |  |  | Monotaro |  |  | 13.939200000000001 | https://www.monotaro.com/p/5068/7148/
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
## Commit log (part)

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2025-03-19 Add Help link in Help dialog.
2025-03-19 Added.
2025-03-19 Deleted.
2025-03-19 Add excluded.
2025-03-19 Updated.
2025-03-19 Fix HELP_LINK.
2025-03-20 Fixed.
2025-03-20 ver.0.14.
2025-03-21 Fix segfault.
2025-03-21 Fix bulk transfer error for FE 2CH.
2025-03-26 Fixed #45.
2025-03-27 Add default values of log_mask.
2025-03-27 http -> https.
2025-03-30 Fixed #40.
2025-03-30 Fixed sampling rate option disabled.
2025-04-08 Fixed segfault for INT8X2 format input.
2025-04-13 Fixed #39.
2025-09-26 sdr_corr_max: match header arg order to impl
2025-11-11 Updated types.
2025-11-11 Support IBYTE, ISHORT as input formats.
2025-11-11 fix symbol table access violation problem
2025-11-19 Update constants, types, APIs.
2025-11-19 Improved carrier-phase coherency.
2025-11-19 Minor fix.
2025-11-19 Fixed comment.
2025-11-19 add API sdr_cpx_fft(), modify API sdr_tag_read(), sdr_tag_write()
2025-11-19 Update time offsets.
2025-11-19 Enabled L1C/B for PVT.
2025-11-19 support alternative RF frontends.
2025-11-19 support alternative RF frontends
2026-04-18 Refactored.
2026-04-18 Change API name.
2026-04-19 Added jammers.
2026-04-22 Added API sdr_lpf_new(), sdr_lpf_free(), sdr_lpf_apply().
2026-04-22 Followed thread API changes.
2026-04-22 Add Galileo E5a-QP.
2026-04-22 Followed thread API change.
2026-04-22 Added API sdr_thread_create(), sdr_thread_join(), sdr_mutex_init(), sdr_mutex_lock(), sdr_mutex_unlock().
2026-04-22 Localized CyAPI.
2026-04-22 Added [CHALL] section.
2026-04-22 Updated types, APIs.
2026-04-22 Updated ant body-fixed frame.
2026-04-22 Added LPF for RF CHs.
2026-04-25 Improve codes.
2026-04-25 Update comments.
2026-04-25 Added RTCM3 RF CH separation.
2026-04-25 Fix TCP client stream bug.
2026-04-26 ver.0.15b.
2026-04-26 Added constant FILT_CN0.
2026-04-26 LS -> KF.
2026-04-26 Added composite array CH.
2026-04-26 Added array options.
2026-04-26 improve performance.
2026-04-26 Updated error massages.
2026-04-28 Moved from build.
2026-04-28 Added libpocketfft.mk
2026-04-28 Use $<.
2026-04-29 Zero fill for dropped samples.
2026-04-30 Move libusb_transfer to sdr_usb.c.
2026-04-30 SDR_MAX_BUFF -> SDR_MAX_UBUFF.
2026-04-30 Follows API changes.
2026-04-30 Added ELE GAIN.
2026-04-30 Fixed typo.
2026-04-30 Added option -b.
2026-04-30 Added API sdr_corr_std_cpx_code().
2026-04-30 Supported E5ABQ.
2026-04-30 Added E5ABQ.
2026-04-30 Update types.
2026-05-01 Fix bugs.
2026-05-01 Fix bug.
2026-05-01 Suppress warning.
2026-05-01 Change array scale.
2026-05-02 Refactored array calibration and beam-forming.
2026-05-02 Add E5ABQ.
2026-05-02 Add plot_image(), plot_sky_mask().
2026-05-02 Refactored array calibration / beam-forming API.
    Move calib save/load into libsdr (sdr_array_{save,load}_calib +
    sdr_rcv wrappers), split sdr_array_config into sdr_array_run /
    sdr_array_inject, drop redundant nrfch parameter (snapshot in
    sdr_array_t), strip obs screening already covered by build_meas,
    and prune internal NULL guards now that callers are validated.
2026-05-02 Updated API reference for array calibration / beam-forming refactor.
2026-05-02 Update comment.
2026-05-02 Refactored array calibration / beam-forming API.
    Renamed: sdr_array_step -> sdr_array_calib (merged with the now-static
    old sdr_array_calib body), sdr_array_inject -> sdr_array_set,
    sdr_array_{save,load}_calib -> sdr_array_{save,load}, and the matching
    sdr_rcv_array_calib -> sdr_rcv_array_run / sdr_rcv_array_step ->
    sdr_rcv_array_calib / sdr_rcv_array_{save,load}_calib ->
    sdr_rcv_array_{save,load}. Per-arch beam initialization moved out of
2026-05-02 Speed up array beam combining and clean up array API.
    Beam combining: precompute per-CH 256-entry LUT (cpx8 byte ->
    weighted (re, im) contribution) in sdr_arch_set_beam() and reduce
    sdr_arch_combine() to load + add. Measured ~2x throughput improvement
    at narch=8 (52.7 -> 104 MB/s in 10x file playback), giving ~1.6x
    real-time margin at fs=16 MHz x 8 array CHs. Re/im pair stored
    interleaved as sdr_lut_t for locality.
2026-05-02 Update trace level.
2026-05-02 ver.0.15.
2026-05-02 Moved to ../build_msvc.
2026-05-03 Fix bug on generating sec-code index.
2026-05-03 Fix problem to overflow obs data buffer in array.
2026-05-03 Add rise of timer resolution for Windows.
2026-05-04 switch includes for FFT.
2026-05-04 Move AltBOC related codes to sdr_ch.c.
2026-05-04 Fallback KF to LS if residual RMS exceeds limit.
2026-05-04 Output $CH log without PVT fix.
2026-05-04 Support E5 AltBOC, DLL, PLL filter -> 2nd, 3rd order.
2026-05-04 Update constants and types.
2026-05-04 Change API sdr_rcv_sel_ch().
2026-05-04 Upgrade correlator plot.
2026-05-04 ver.0.15b2
2026-05-04 Follow API change.
2026-05-04 ver.0.15b2.
2026-05-05 Add scale in correlation plot.
2026-05-05 Add receiver option -BUMP_K=.
2026-05-05 Add E5a-E5b offset correction for AltBOC.
2026-05-05 Update blank line.
2026-05-06 Update global options.
2026-05-06 Adjust layout.
2026-05-06 Array Calibration enable if narch <= 0.
2026-05-06 Fix label.
2026-05-07 Add array calibration modes.
2026-05-07 Add Clear button in Array Option dialog.
2026-05-07 matplotlib -> sdr_plot.py.
2026-05-07 Add I * sign(IP) average for correlator statistics.
2026-05-07 Add AveI for correlator plot.
2026-05-08 Fix style.
2026-05-08 Fix bump-jump for G1OCP, G2OCP.
2026-05-09 Fix unrecognized PlutoSDR in RaspiOS.
2026-05-09 Adjust button size.
2026-05-09 Change widget style for macOS and Linux.
2026-05-09 -Ofast -> -O3.
2026-05-09 sprintf() -> snprintf().
2026-05-09 Refer command_ref.md.
2026-05-09 Fix macOS problem.
2026-05-09 Moved to pocket_trk.sh.
2026-05-09 Fix maxOS problem.
2026-05-09 Supress warnings.
2026-05-09 Supress warning.
2026-05-09 fftw3 -> pocketfft.
2026-05-09 fftw -> pocketfft.
2026-05-11 Add soapy log.
2026-05-11 IQ independent AGC.
2026-05-11 v.0.15.
2026-05-11 Update layout.
2026-05-11 Add airspy as device.
2026-05-11 Add -fd option.
2026-05-11 Follow -fd option.
2026-05-11 Moved to lib/SoapySDR.
2026-05-11 Deleted or moved.
2026-05-11 Update sytle. document link: internal -> github.
2026-05-30 Add Airspy Mini.
2026-05-30 Add page break.
2026-05-30 Add support CS16 in read_data.
2026-05-30 Support E5AQP code.
2026-05-30 Add option -fmt.
2026-05-30 Write tag file before capture.
2026-05-30 Fix RF CH assignment bug for FE 4CH (SDR_FMT_RAW16).
2026-06-01 Add almanac decoder functions for GLO,GAL,BDS.
2026-06-01 Add almanac decoder functions.
2026-06-01 Add receiver clock rate in solution.
2026-06-01 Reflect API changes.
2026-06-01 Support SoapySDR devices.
2026-06-01 Add make option USE_SOAPY, USE_FFTW.
2026-06-01 Add make option USE_FFTW.
2026-06-01 Add $ALM log, Fast-Search acquisition mode.
2026-06-01 Add Signal Acquisition Mode in System Options.
2026-06-01 ver.0.16.
2026-06-01 Add #ifdef SOAPYSDR.
2026-06-01 Add almanac decoder for GLO,GAL,BDS.
2026-06-01 Add almanac decoding, save and load.
2026-06-01 Add fast acquisition mode.
2026-06-01 Add $ALM in log_types[].
2026-06-01 Support format CS8 and CS16.
2026-06-01 Add make option USE_FFTW, USE_SOAPY.
2026-06-01 Add option max-acq.
2026-06-01 Change default output logs.
2026-06-01 fix: V-003 security vulnerability
    Automated security fix generated by OrbisAI Security
2026-06-01 fix: add bounds check before memcpy in sdr_nav.c
    The code uses a 'type' variable derived from navigation message content to compute a destination offset for memcpy
2026-06-01 Update Input Options Dialog.
2026-06-01 Fix github latex problem.
2026-06-01 Fix github md viewer latex problem.
2026-06-01 Fix github md parser problems.
2026-06-03 Fix pseudorange offset problem.
2026-06-04 Moved from .. .
2026-06-04 Added for unit tests.
2026-06-04 Moved to ./script or ./python.
2026-06-04 Updates for unit tests.
2026-06-04 Update directory structure.
2026-06-05 Fix CS16 (little-endian) in IF Data File Formats.
2026-06-06 LDPC-codes -> internal implementation.
2026-06-06 LIBFEC -> internal implementation.
2026-06-06 sdr_corr_std performance as np=4.
2026-06-06 Update tests of sdr_decode_conv() and sdr_decode_rs().
2026-06-13 Rise timer resolution for Windows.
2026-06-13 Hard-decision -> soft-decision.
2026-06-13 Update symbol-sync algorithm in symb_sync().
2026-06-14 MAX_RMS: 0.015 -> 0.020.
2026-06-14 Add THRES_SEC_RATIO for sec-code-sync.
2026-06-14 Add receiver option -LOG_LEVEL=n.
2026-06-14 ver.0.17.
2026-06-14 Improved symbol-sync.
2026-06-14 Updated for Linux, macOS.
2026-06-14 Add Options [Load], [Save] buttons.
2026-06-14 Add [Set Default] in System Options, [Set All], [Unset All] in Signal Options.
2026-06-14 Added for Codex and Claude Code.
2026-06-15 Update START, STOP log.
2026-06-15 Update symbol sync logic.
2026-06-15 Update loss-of-lock detection logic.
2026-06-15 Add system option Carrier Lock Threshold (PLI) and Lost Decision Count (windows).
2026-06-15 Add system options.
2026-06-17 Remove link of libfec.a and libldpc.a.
2026-06-17 Add options thres_pli and lost_th.
2026-06-17 Add phi to sdr_ch_t.
2026-06-17 Update style.
2026-06-17 Add PLI in print_ch_stat().
2026-06-17 Fix carrier phase update logic. Fix bug to switch WB_FLL and NB_FLL.
2026-06-17 Add [To RINEX] button in Output Options dialog.
2026-06-17 Fix carrier phase logic in tracking loop.
2026-06-17 Default lag_epoch option: 0.5 -> 0.8 s.
2026-06-17 Suppress warnings.
2026-06-17 Add make option USE_AVX2=x.
2026-06-17 Update UI layout.
2026-06-17 Fix invalid pseudorange.
2026-06-18 No output $OBS if pseudorange missing.
2026-06-18 Update time offset table.
2026-06-19 Update Documents.
2026-06-19 Fix document URL.
2026-06-19 Fix URL path.
2026-06-21 LO Freq input: Entry -> Combobox in Input Options Dialog.
